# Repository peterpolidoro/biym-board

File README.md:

- [About](#org1d32820)
- [Images](#org6a9f21d)
- [Schematic](#orgaac9f41)
- [PCB](#org3dfe019)
- [Bill of Materials](#org53f6dab)
- [Development](#orgc712f8c)

    <!-- This file is generated automatically from .metadata.org -->
    <!-- File edits may be overwritten! -->

# About

```markdown
- Project Name: biym-board
- Synopsis: PCB files for biym game.
- Pcb Version: 1.3
- Release Date: 2024-05-16
- Creation Date: 2022-10-28
- License: GPL-3.0
- URL: https://github.com/peterpolidoro/biym-board
- Author: Peter Polidoro
- Email: peter@polidoro.io
- Copyright: 2024 Peter Polidoro
- References:
  - https://www.kicad.org/
  - https://www.adafruit.com/product/4062
  - https://learn.adafruit.com/adafruit-feather/feather-specification
  - https://github.com/adafruit/Adafruit-nRF52-Bluefruit-Feather-PCB
```

# Images

# Schematic

[./documentation/schematic/biym-board.pdf](./documentation/schematic/biym-board.pdf)

# PCB

# Bill of Materials

|    |
|--- |
|  |

# Development

1.  Install Guix.

[Install Guix](https://guix.gnu.org/manual/en/html_node/Binary-Installation.html)

1.  Clone repository.

```sh
git clone https://github.com/peterpolidoro/biym-board
cd biym-board
```

1.  Open project in KiCad

```sh
make project-edits
exit
```

. Open .metadata.org.

```sh
make metadata-edits
```

1.  Modify project specific variables.

```sh
make metadata
```

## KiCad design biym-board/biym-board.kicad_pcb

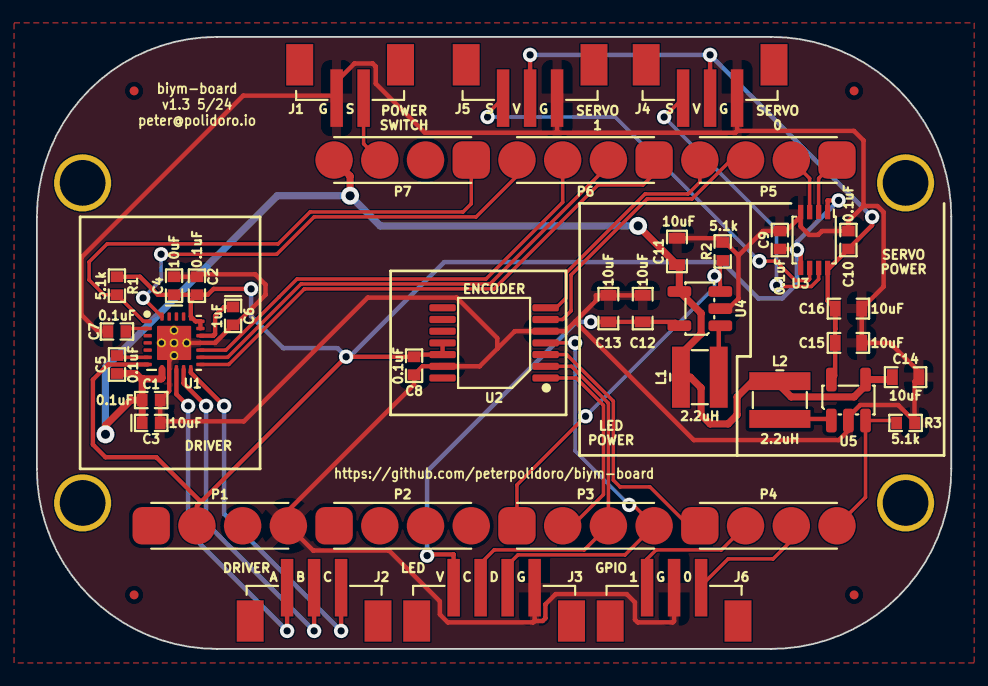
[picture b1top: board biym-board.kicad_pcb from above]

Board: 2 copper layers, 50.8 x 34.0 mm, 44 parts (0 on the bottom side), 33 nets.

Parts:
C1, C2, C5, C7, C8, C9, C10: 0.1uF; SM0402
C3, C4: 10uF; SM0402_POL
C6: 1uF; SM0402_POL
C11, C12, C13, C14, C15, C16: 10uF; SM0603
FID1, FID2, FID3, FID4: FIDUCIAL_0.5mm_MASK1mm; FIDUCIAL_0.5mm_Mask1mm
FW1: FEATHERWING_nRF52; FEATHERWING
J1: HEADER_01X02_JST_ZH_SMD_VERTICAL; JST_ZH_B2B_ZR_SM4_TF_1x02-1MP_P1.50mm_Vertical
J2, J4, J5, J6: HEADER_01X03_JST_ZH_SMD_VERTICAL; JST_ZH_B3B_ZR_SM4_TF_1x03-1MP_P1.50mm_Vertical
J3: HEADER_01X04_JST_ZH_SMD_VERTICAL; JST_ZH_B4B_ZR_SM4_TF_1x04-1MP_P1.50mm_Vertical
L1, L2: 2.2uH; INDUCTOR_VLS_HBX
P1, P2, P3, P4, P5, P6, P7: POGO_01X04_0.1IN_1_SMD; POGO_01x04_0.1in_SMD
R1, R2, R3: 5.1k; SM0402
U1: DRV8311H; WQFN-24-1EP_3x3mm_P0.4mm_EP1.9x1.9mm_ThermalVias
U2: AS5047P; TSSOP-14_4.4x5mm_P0.65mm
U3: LT_SN74LVC2T45DCUT; VSSOP-8_2.4x2.1mm_P0.5mm
U4, U5: BOOST_5V_RP402N501F; SOT-23-5

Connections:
/DRIVER_PWM_A: P6.3, U1.15 (INHA)
/DRIVER_PWM_B: P6.2, U1.14 (INHB)
/DRIVER_PWM_C: P6.1, U1.13 (INHC)
/ENABLE_LED_POWER: P3.1, R2.1, U4.3 (CE)
/ENABLE_SERVO_POWER: P4.4, R3.1, U5.3 (CE)
/ENCODER_A: P5.4, U2.7 (A)
/ENCODER_B: P5.3, U2.6 (B)
/GND: C1.2, C2.2, C3.2, C4.2, C6.2, C7.2, C8.2, C9.2, C10.2, C11.2, C12.2, C13.2, C14.2, C15.2, C16.2, J1.1, J3.1, J4.3, J5.3, J6.2, P1.4, R2.2, R3.2, U1.9 (PGND), U1.16 (AGND), U1.25 (PAD), U2.5 (TEST), U2.13 (GND), U3.4 (GND), U4.2 (GND), U5.2 (GND)
/GPIO_0: J6.1, P4.3
/GPIO_1: J6.3, P4.2
/MISO: P4.1, U2.3 (MISO)
/MOSI: J3.2, P3.4, U2.4 (MOSI)
/SCK: J3.3, P3.3, U2.2 (CLK)
/SERVO_SIGNAL_0: P5.1, U3.2 (A1)
/SERVO_SIGNAL_1: P5.2, U3.3 (A2)
/VBATTERY: C1.1, C3.1, C5.1, C11.1, C14.1, L1.1, L2.1, P7.4, U1.8 (VM), U4.4 (VIN), U5.4 (VIN)
/VDIGITAL: C2.1, C4.1, C8.1, C9.1, P1.2, R1.1, U1.7 (VIN_AVDD), U1.18 (INLA), U1.19 (INLB), U1.20 (INLC), U2.11 (VDD), U2.12 (VDD3V3), U3.1 (VCCA), U3.5 (DIR)
/VLED: C12.1, C13.1, J3.4, U4.5 (VOUT)
/VSERVO: C10.1, C15.1, C16.1, J4.2, J5.2, U3.8 (VCCB), U5.5 (VOUT)
/driver/CP: C5.2, U1.6 (CP)
/driver/CSAREF: C7.1, U1.2 (CSAREF)
/driver/MOTOR_A: J2.3, U1.10 (OUTA)
/driver/MOTOR_B: J2.2, U1.11 (OUTB)
/driver/MOTOR_C: J2.1, U1.12 (OUTC)
/driver/VDD: C6.1, U1.17 (AVDD)
/power/boost-led/LX: L1.2, U4.1 (LX)
/power/boost-servo/LX: L2.2, U5.1 (LX)
/servo/TRANSLATED_SIGNAL_0: J4.1, U3.7 (B1)
/servo/TRANSLATED_SIGNAL_1: J5.1, U3.6 (B2)
/~DISABLE_ALL_POWER: J1.2, P7.3
/~DRIVER_FAULT: P7.1, R1.2, U1.1 (~FAULT)
/~DRIVER_SLEEP: P6.4, U1.24 (~SLEEP)
/~ENCODER_CS: P3.2, U2.1 (~CS)

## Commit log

2022-10-29 Update metadata
2022-10-30 Initial Kicad project files
2022-10-30 shell must be pure to get the correct enviroment variables
2022-10-30 Update references
2022-10-31 Run kicad in pure shell instead of container
2022-11-01 Try container options
2022-11-02 Move board files
2022-11-08 Update channels
2022-11-08 Reorganize metadata
2022-11-09 Add some datasheets
2022-11-09 Add power stage
2022-11-09 Add power
2022-11-10 Change diodes
2022-11-11 Switch feather contacts to pogo pins
2022-11-11 Add motor sheet
2022-11-14 More motor driver wiring
2022-11-14 Rename reference files
2022-11-14 Add driver external components
2022-11-14 Initial driver wiring
2022-11-14 Add motor feedback
2022-11-15 Rename sheets
2022-11-15 Add led sheet
2022-11-16 Wire led sheet
2022-11-16 Add boosted voltage
2022-11-16 servo -> output
2022-11-17 output -> servo
2022-11-17 Finished v0.1 of schematic
2022-11-18 Check if there is room for connectors
2022-11-18 Move gpio pins to rx and tx pins
2022-11-19 Add boost for both led and servo
2022-11-19 Initial footprint placement
2022-11-19 Initial v1.0 layout
2022-11-20 Add board images
2022-11-20 Moved some traces away from the encoder
2022-11-20 Completed v1.1 layout
2022-11-20 Adjust after circuithub import test
2022-11-21 Finished v1.2
2022-11-21 Add invoices
2022-11-21 Update board images
2022-11-21 Reorganize documentation
2022-11-22 Crop pcb svg files
2022-11-22 Convert pcb svg files to png
2022-11-22 Increase svg -> png dpi
2022-11-28 Test metadata changes
2022-11-29 Update license
2022-11-29 Update version number
2022-12-05 Updated metadata file
2022-12-06 Update dimensions
2022-12-13 Add pcb-photo.png
2024-05-17 Update to kicad 7
